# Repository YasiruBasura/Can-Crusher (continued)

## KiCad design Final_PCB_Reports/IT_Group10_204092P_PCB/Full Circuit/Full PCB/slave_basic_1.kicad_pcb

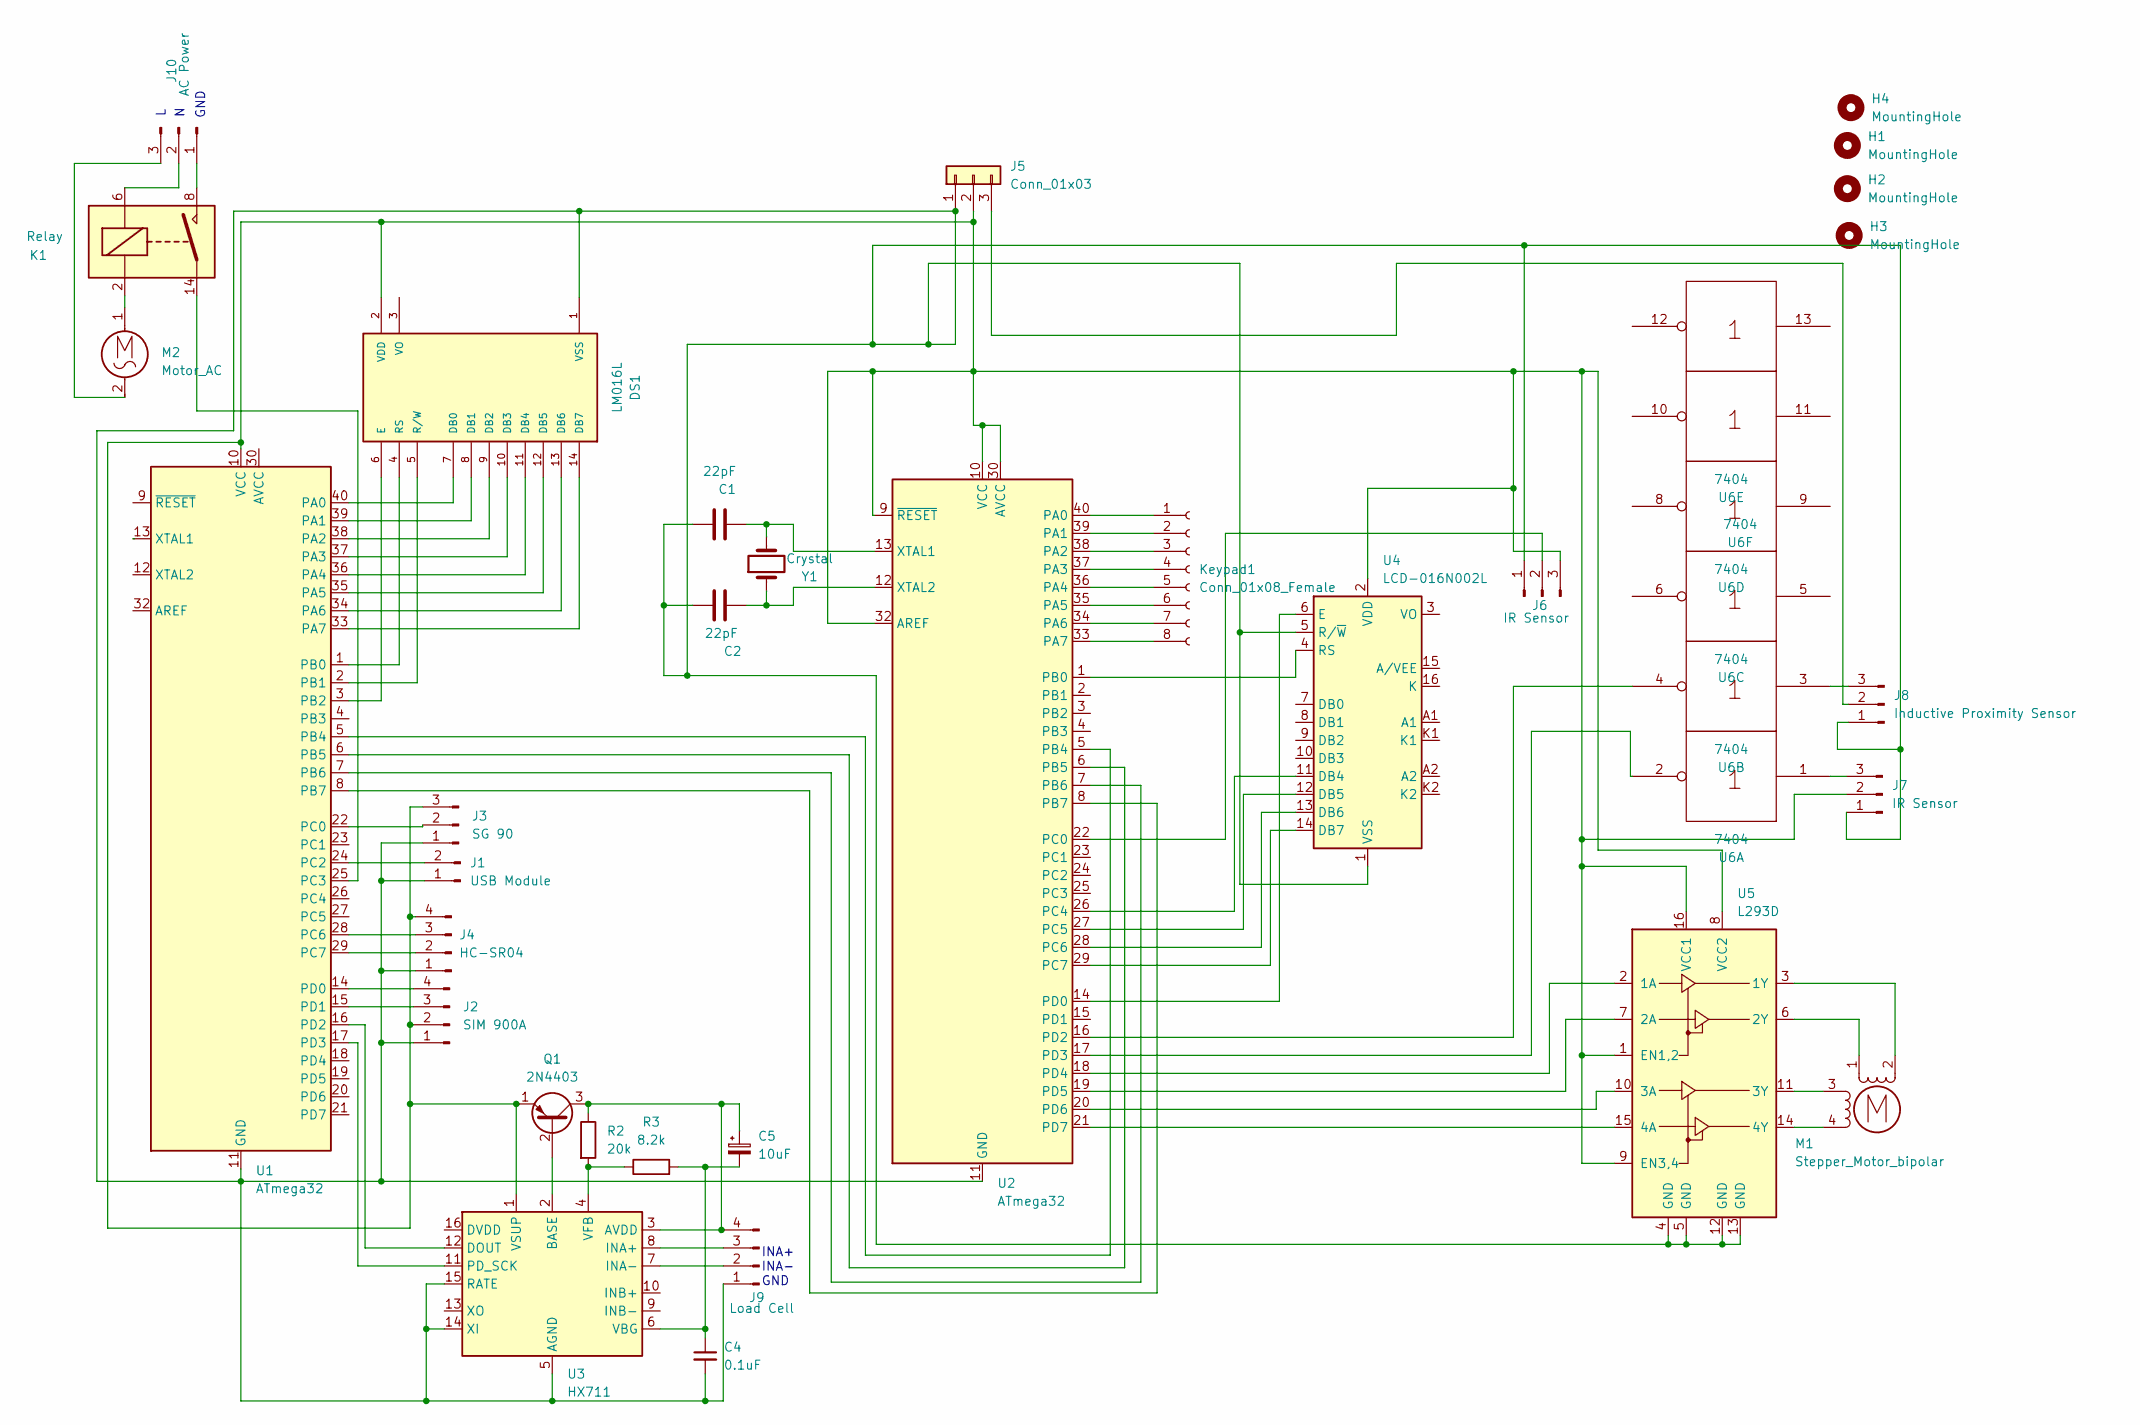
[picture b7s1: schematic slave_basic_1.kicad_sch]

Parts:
C1, C2: 22pF; CP_Radial_D4.0mm_P1.50mm
C4: 0.1uF; CP_Radial_D4.0mm_P1.50mm
C5: 10uF; CP_Radial_D4.0mm_P1.50mm
DS1: LM016L; LCD_LM016L
H1, H2, H3, H4: MountingHole; MountingHole_3.5mm_Pad
J1: USB Module; PinSocket_1x02_P1.27mm_Vertical
J2: SIM 900A; PinSocket_1x04_P1.27mm_Vertical
J3: SG 90; PinSocket_1x03_P1.27mm_Vertical
J4: HC-SR04; PinSocket_1x04_P1.27mm_Vertical
J5: Conn_01x03; PinSocket_1x03_P2.54mm_Vertical
J6, J7: IR Sensor; PinSocket_1x03_P1.27mm_Vertical
J8: Inductive Proximity Sensor; PinSocket_1x03_P1.27mm_Vertical
J9: Load Cell; PinSocket_1x04_P1.27mm_Vertical
J10: AC Power; PinSocket_1x03_P1.27mm_Vertical
K1: Relay; Relay_StandexMeder_DIP_LowProfile
Keypad1: Conn_01x08_Female; PinSocket_1x08_P1.27mm_Vertical
M1: Stepper_Motor_bipolar; PinSocket_1x04_P1.27mm_Vertical
M2: Motor_AC; PinSocket_1x02_P2.54mm_Vertical
Q1: 2N4403; TO-92_Inline
R2: 20k; R_Axial_DIN0204_L3.6mm_D1.6mm_P5.08mm_Horizontal
R3: 8.2k; R_Axial_DIN0204_L3.6mm_D1.6mm_P5.08mm_Horizontal
U1, U2: ATmega32; DIP-40_W15.24mm
U3: HX711; DIP-14_W7.62mm
U4: LCD-016N002L
U5: L293D; DIP-16_W7.62mm
U6: 7404; DIP-14_W7.62mm
Y1: Crystal; Crystal_AT310_D3.0mm_L10.0mm_Vertical

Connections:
Gnd: U6.7 (Gnd), U6.14 (Vcc)
unnamed: C1.1, C2.1, C4.2, DS1.1 (VSS), J1.1, J2.1, J3.1, J4.1, J5.1, J6.1, J7.1, J8.1, J9.1, U1.11 (GND), U1.31 (GND), U2.11 (GND), U2.31 (GND), U3.5 (AGND), U3.14 (XI), U3.15 (RATE), U4.1 (VSS), U4.5 (R/~W), U5.4 (GND), U5.5 (GND), U5.12 (GND), U5.13 (GND)
unnamed: C1.2, U2.13 (XTAL1), Y1.2
unnamed: C2.2, U2.12 (XTAL2), Y1.1
unnamed: C4.1, C5.2, R3.2, U3.6 (VBG)
unnamed: C5.1, J9.4, Q1.3 (C), R2.1, U3.3 (AVDD)
unnamed: DS1.2 (VDD), J2.2, J3.3, J4.4, J5.2, J6.3, J7.2, Q1.1 (E), U1.10 (VCC), U2.9 (~RESET), U2.10 (VCC), U2.30 (AVCC), U2.32 (AREF), U3.1 (VSUP), U4.2 (VDD), U5.1 (EN1,2), U5.8 (VCC2), U5.9 (EN3,4), U5.16 (VCC1)
unnamed: DS1.4 (RS), U1.1 (PB0)
unnamed: DS1.5 (R/W), U1.2 (PB1)
unnamed: DS1.6 (E), U1.3 (PB2)
unnamed: DS1.7 (DB0), U1.40 (PA0)
unnamed: DS1.8 (DB1), U1.39 (PA1)
unnamed: DS1.9 (DB2), U1.38 (PA2)
unnamed: DS1.10 (DB3), U1.37 (PA3)
unnamed: DS1.11 (DB4), U1.36 (PA4)
unnamed: DS1.12 (DB5), U1.35 (PA5)
unnamed: DS1.13 (DB6), U1.34 (PA6)
unnamed: DS1.14 (DB7), U1.33 (PA7)
unnamed: J1.2, U1.24 (PC2)
unnamed: J2.3, U1.15 (PD1)
unnamed: J2.4, U1.14 (PD0)
unnamed: J3.2, U1.22 (PC0)
unnamed: J4.2, U1.29 (PC7)
unnamed: J4.3, U1.28 (PC6)
unnamed: J5.3, J8.2
unnamed: J6.2, U2.22 (PC0)
unnamed: J7.3, U6.1
unnamed: J8.3, U6.3
unnamed: J10.1, K1.8
unnamed: J10.2, K1.6
unnamed: J10.3, M2.2
unnamed: K1.2, M2.1
unnamed: Keypad1.1, U2.40 (PA0)
unnamed: Keypad1.2, U2.39 (PA1)
unnamed: Keypad1.3, U2.38 (PA2)
unnamed: Keypad1.4, U2.37 (PA3)
unnamed: Keypad1.5, U2.36 (PA4)
unnamed: Keypad1.6, U2.35 (PA5)
unnamed: Keypad1.7, U2.34 (PA6)
unnamed: Keypad1.8, U2.33 (PA7)
unnamed: M1.1, U5.6 (2Y)
unnamed: M1.2 (-), U5.3 (1Y)
unnamed: M1.3, U5.11 (3Y)
unnamed: M1.4, U5.14 (4Y)
unnamed: Q1.2 (B), U3.2 (BASE)
unnamed: R2.2, R3.1, U3.4 (VFB)
unnamed: U1.5 (PB4), U2.5 (PB4)
unnamed: U1.6 (PB5), U2.6 (PB5)
unnamed: U1.7 (PB6), U2.7 (PB6)
unnamed: U1.8 (PB7), U2.8 (PB7)
unnamed: U1.16 (PD2), U3.12 (DOUT)
unnamed: U1.17 (PD3), U3.11 (PD_SCK)
unnamed: K1.14, U1.25 (PC3)
unnamed: U2.1 (PB0), U4.4 (RS)
unnamed: U2.14 (PD0), U4.6 (E)
unnamed: U2.16 (PD2), U6.4
unnamed: U2.17 (PD3), U6.2
unnamed: U2.18 (PD4), U5.2 (1A)
unnamed: U2.19 (PD5), U5.7 (2A)
unnamed: U2.20 (PD6), U5.10 (3A)
unnamed: U2.21 (PD7), U5.15 (4A)
unnamed: U2.26 (PC4), U4.11 (DB4)
unnamed: U2.27 (PC5), U4.12 (DB5)
unnamed: U2.28 (PC6), U4.13 (DB6)
unnamed: U2.29 (PC7), U4.14 (DB7)
unnamed: J9.2, U3.7 (INA-)
unnamed: J9.3, U3.8 (INA+)

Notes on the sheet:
INA+ INA- GND
GND

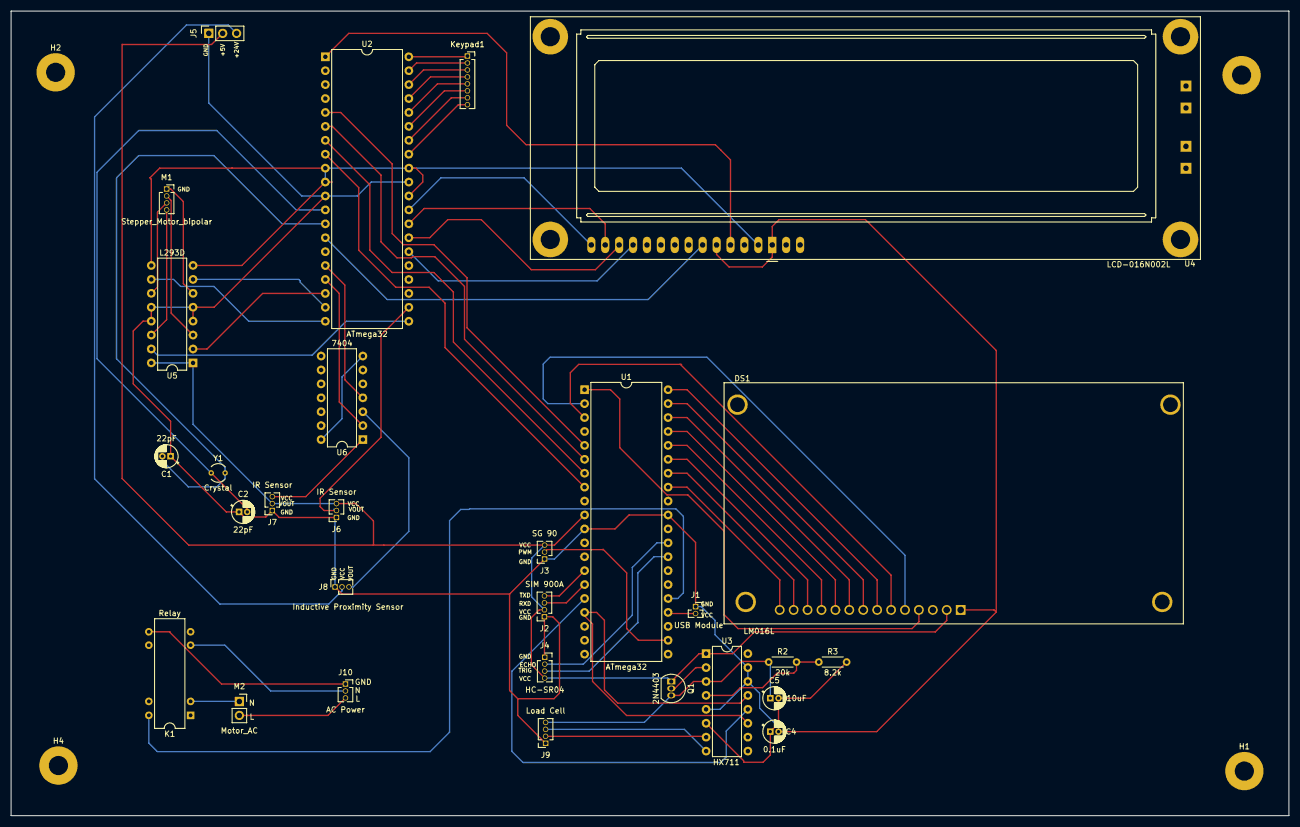
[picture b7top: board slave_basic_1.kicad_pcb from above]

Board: 2 copper layers, 233.2 x 146.8 mm, 33 parts (0 on the bottom side), 67 nets.

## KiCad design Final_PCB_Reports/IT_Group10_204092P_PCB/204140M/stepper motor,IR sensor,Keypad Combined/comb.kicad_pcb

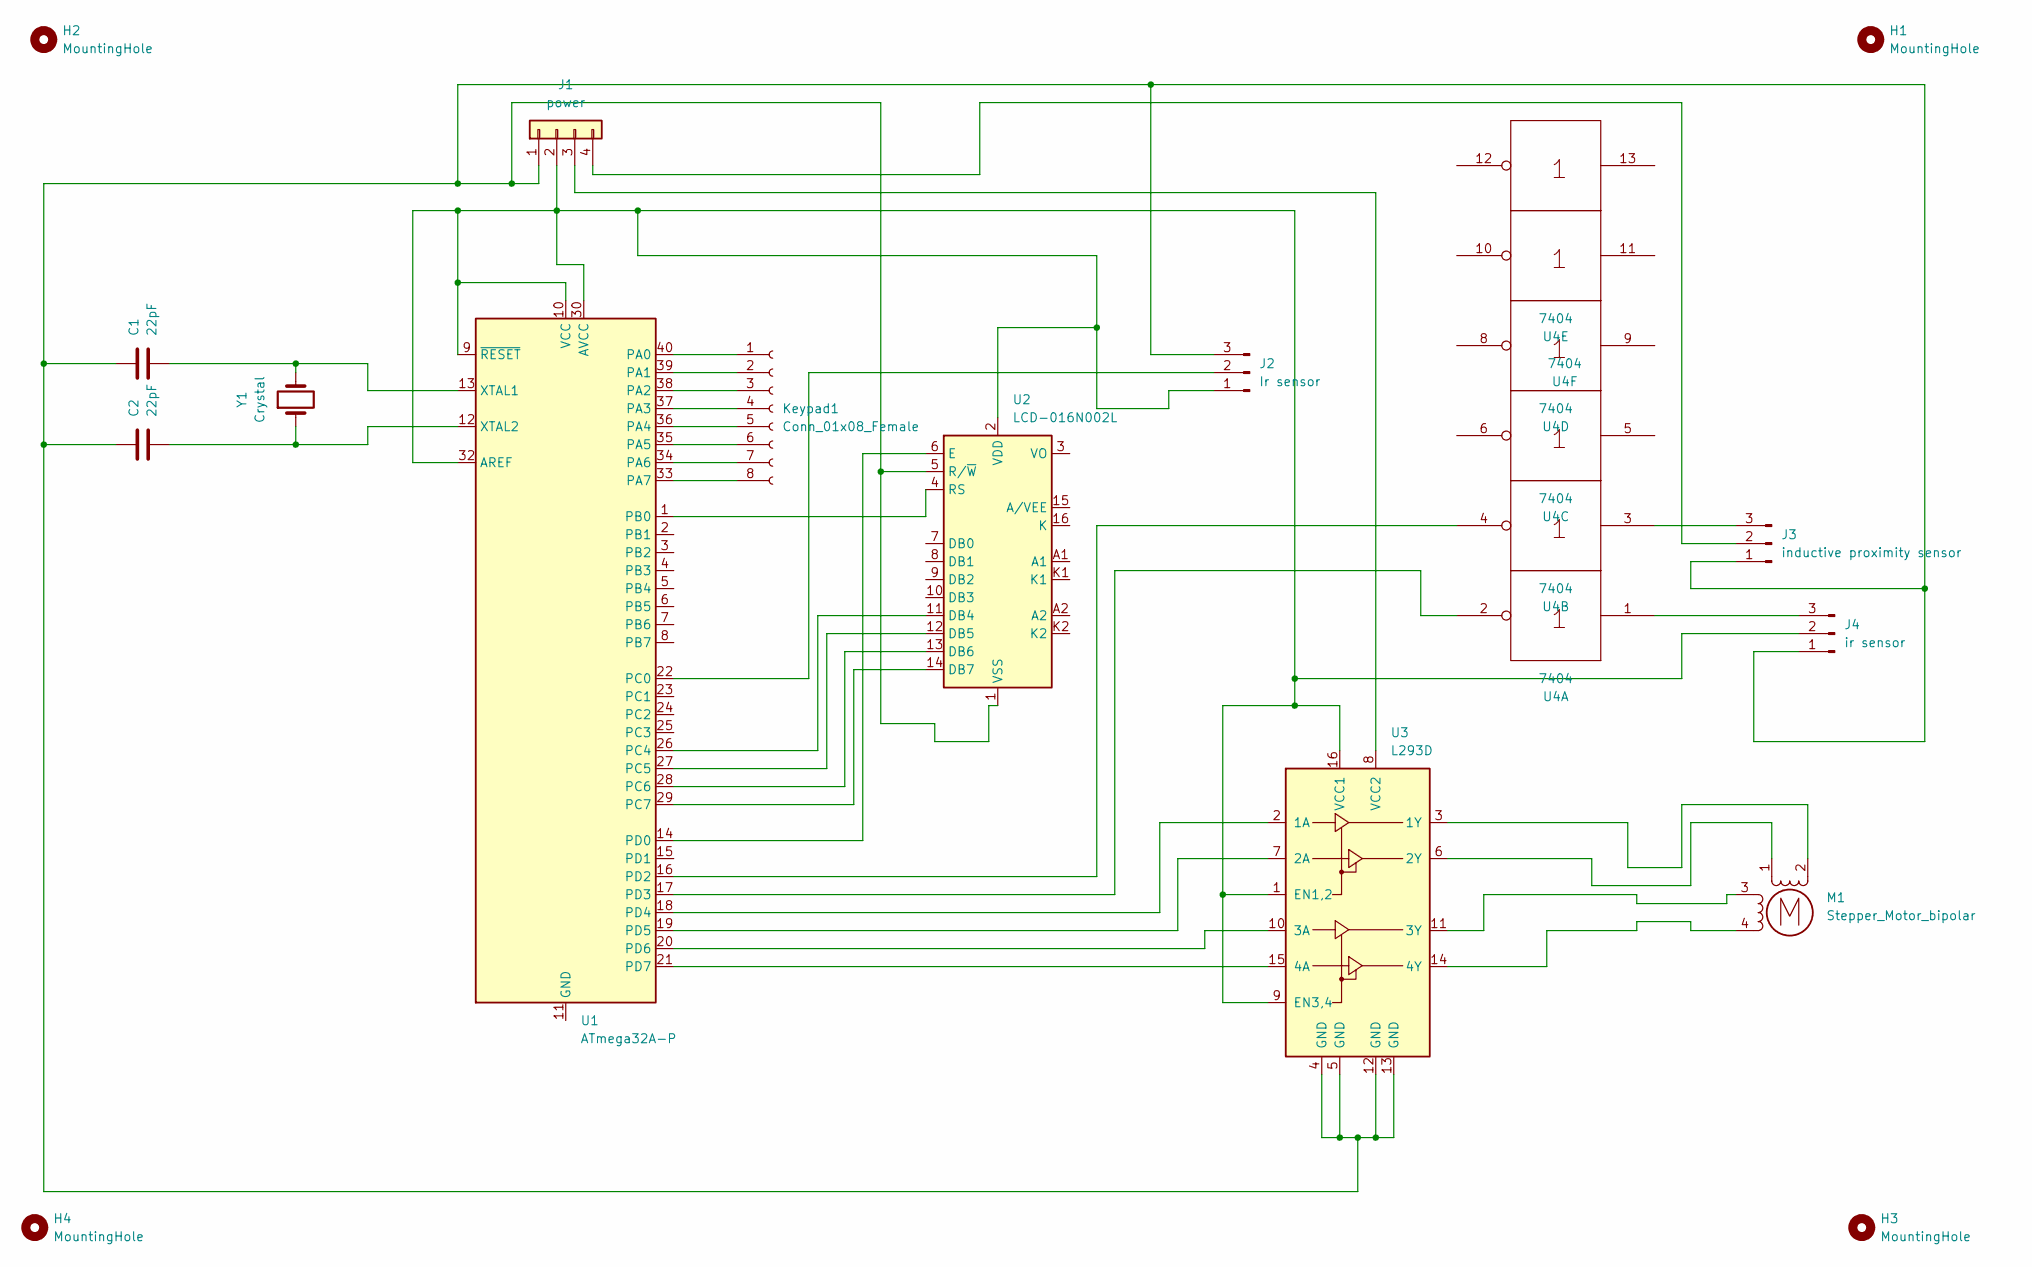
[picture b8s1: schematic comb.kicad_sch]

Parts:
C1, C2: 22pF; CP_Radial_D4.0mm_P1.50mm
H1, H2, H3, H4: MountingHole; MountingHole_3.5mm_Pad
J1: power; PinHeader_1x04_P2.54mm_Horizontal
J2: Ir sensor; PinSocket_1x03_P1.27mm_Vertical
J3: inductive proximity sensor; PinSocket_1x03_P1.27mm_Vertical
J4: ir sensor; PinSocket_1x03_P1.27mm_Vertical
Keypad1: Conn_01x08_Female; PinSocket_1x08_P1.27mm_Vertical
M1: Stepper_Motor_bipolar; PinSocket_1x04_P1.27mm_Vertical
U1: ATmega32A-P; DIP-40_W15.24mm
U2: LCD-016N002L
U3: L293D; DIP-16_W7.62mm
U4: 7404; DIP-14_W7.62mm
Y1: Crystal; Crystal_AT310_D3.0mm_L10.0mm_Vertical

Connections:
Gnd: U4.7 (Gnd), U4.14 (Vcc)
unnamed: C1.1, C2.1, J1.1, J2.3, J3.1, J4.1, U2.1 (VSS), U2.5 (R/~W), U3.4 (GND), U3.5 (GND), U3.12 (GND), U3.13 (GND)
unnamed: C1.2, U1.13 (XTAL1), Y1.2
unnamed: C2.2, U1.12 (XTAL2), Y1.1
unnamed: J1.2, J2.1, J4.2, U1.9 (~RESET), U1.10 (VCC), U1.30 (AVCC), U1.32 (AREF), U2.2 (VDD), U3.1 (EN1,2), U3.9 (EN3,4), U3.16 (VCC1)
unnamed: J1.3, U3.8 (VCC2)
unnamed: J1.4, J3.2
unnamed: J2.2, U1.22 (PC0)
unnamed: J3.3, U4.3
unnamed: J4.3, U4.1
unnamed: Keypad1.1, U1.40 (PA0)
unnamed: Keypad1.2, U1.39 (PA1)
unnamed: Keypad1.3, U1.38 (PA2)
unnamed: Keypad1.4, U1.37 (PA3)
unnamed: Keypad1.5, U1.36 (PA4)
unnamed: Keypad1.6, U1.35 (PA5)
unnamed: Keypad1.7, U1.34 (PA6)
unnamed: Keypad1.8, U1.33 (PA7)
unnamed: M1.1, U3.6 (2Y)
unnamed: M1.2 (-), U3.3 (1Y)
unnamed: M1.3, U3.11 (3Y)
unnamed: M1.4, U3.14 (4Y)
unnamed: U1.1 (PB0), U2.4 (RS)
unnamed: U1.11 (GND), U1.31 (GND)
unnamed: U1.14 (PD0), U2.6 (E)
unnamed: U1.16 (PD2), U4.4
unnamed: U1.17 (PD3), U4.2
unnamed: U1.18 (PD4), U3.2 (1A)
unnamed: U1.19 (PD5), U3.7 (2A)
unnamed: U1.20 (PD6), U3.10 (3A)
unnamed: U1.21 (PD7), U3.15 (4A)
unnamed: U1.26 (PC4), U2.11 (DB4)
unnamed: U1.27 (PC5), U2.12 (DB5)
unnamed: U1.28 (PC6), U2.13 (DB6)
unnamed: U1.29 (PC7), U2.14 (DB7)

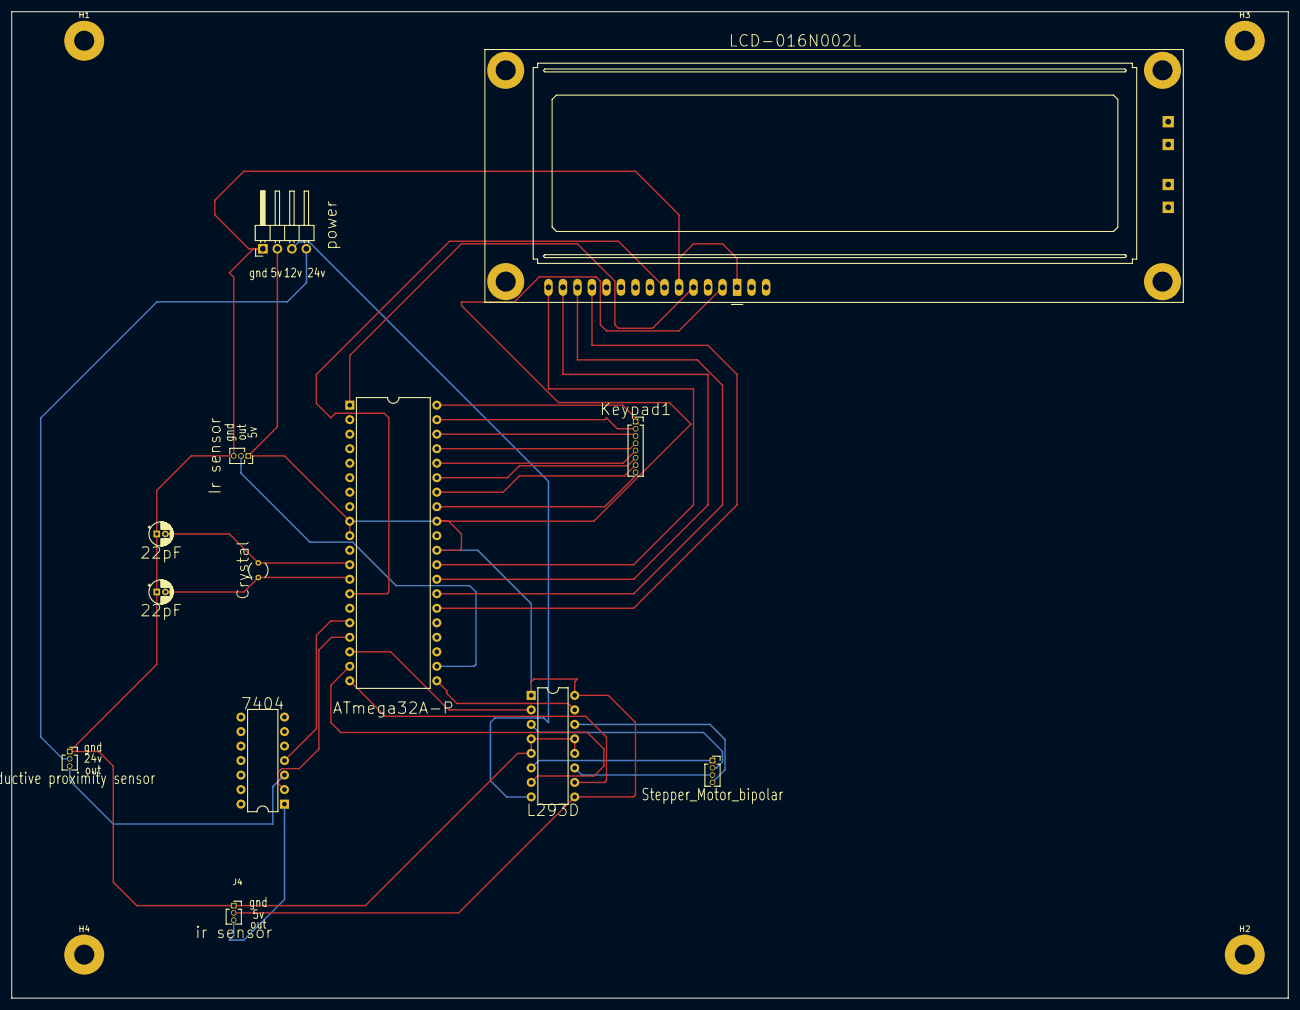
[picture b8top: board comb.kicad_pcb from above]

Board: 2 copper layers, 223.5 x 172.7 mm, 17 parts (0 on the bottom side), 35 nets.

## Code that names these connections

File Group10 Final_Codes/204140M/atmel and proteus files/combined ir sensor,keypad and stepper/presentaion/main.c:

#ifndef F_CPU

#define F_CPU 16000000UL //freaquency of external crystal

#endif
#include <avr/io.h>
#include <util/delay.h>



//define interfacing pins between L293D and ATmega32

#define a1 (1<<PD4)

#define a2 (1<<PD5)

#define a3 (1<<PD6)

#define a4  (1<<PD7)



//For switch

#define SW (1<<PD3)    //Ir
#define SW2 (1<<PD2)   //ALL validation

//lcd and key board
#define LCD PORTC
#define EN 0
#define RS 0
#define RW 1

 int get_pn;
 //int get_cn;//number of cans
 char can_no[10];
 

unsigned char keypad();
int keypad_func(){
	unsigned char x;
	char no[10];
	int i=0;
	int i1=0;
	DDRA =0x0F; // make PA0 to PA3 = output and PA4 to PA7 = Input
	lcd_init();
	while(1){
		PORTA=0xF0; // make all 4 column 1 and all rows 0
		if(PINA!= 0xF0){
			_delay_ms(5);
			x=keypad();
			if (x=='*')
			{
				lcdcmd(0x01);//clear lcd
				lcdcmd(0x80);//set the curser to first line
				lcd_Print("1-Fast Charge");
				lcdcmd(0xc0);//set the curser to second line
				lcd_Print("2-Ez Cash");
				_delay_ms(100);
				lcdcmd(0x01);
				lcdcmd(0x80);//set the curser to first line
				lcd_Print("3-Donate");
				
				while(1){
					if(PINA!= 0xF0){
						x=keypad();
						//charge
						if(x=='1'){
							_delay_ms(5);
							lcdcmd(0x80);//set the curser to first line
							lcd_Print(" ");
							lcdcmd(0x01);//clear lcd
							break;
						}
						//easy cash
						else if(x=='2'){
							get_pn=1;//get phone no
							_delay_ms(5);
							lcdcmd(0x80);//set the curser to first line
							lcd_Print(" ");
							lcdcmd(0x01);//clear lcd
							lcd_Print("Enter the Phone");
							lcdcmd(0xc0);
							lcd_Print("Number");
							lcdcmd(0x80);
							_delay_ms(100);
							lcdcmd(0x01);
							lcd_Print("Press = to");
							lcdcmd(0xc0);
							lcd_Print("Finish");
							lcdcmd(0x80);
							_delay_ms(100);
							lcdcmd(0x01);
							break;
						}
						//donate
						else if(x=='3'){
							
						}
						
					}
					/*else
					{
						lcddata(x);
						
					}*/

				}
				
				
			}
			else if (x=='=')
			{
				
				
				get_pn=0;
				lcdcmd(0x01);
				lcd_Print("Entered phone NO.:");
				lcdcmd(0xc0);
				lcd_Print(&no);//print the no
				lcdcmd(0x80);
				//lcd_Print(&can_no);//print the no
				int phone_no= atoi(no);//phone nimber in int
				_delay_ms(100);
				lcdcmd(0x01);
			
				_delay_ms(100);
				lcdcmd(0x01);
				i=0;
				return 0;
				
				
			}
			else
			{
				
				lcddata(x);
				if(get_pn==1){
					no[i]=x;
					i++;
				}
				else{
					can_no[i1]=x;
					i1++;
				}
				
			}
		}
	}
	
}
void lcdcmd(unsigned char cmd){
	PORTB &=~(1<<RS); //RS=0 for command (1111 1110)
	PORTB &=~(1<<RW); //RW=0 for write (1111 1101)
	LCD= cmd & 0xF0;  //Send upper nibble
	PORTD|=(1<<EN); //EN=1 for H to L pulse
	_delay_ms(1);
	PORTD &= ~(1<<EN); // EN=0 for H to L pulse

	LCD = cmd<<4; // send low nibble;
	PORTD |=(1<<EN); //EN=0for H to L pulse
	_delay_ms(1);
	PORTD &= ~(1<<EN);
}

void lcd_Print (char*str){
	int i;
	for(i=0;str[i]!=0;i++)		/* Send each char of string till the NULL */
	{
		lcddata(str[i]);
	}
}


void lcddata(unsigned char data){
	PORTB |= (1<<RS); //RS=1 for data
	PORTB &= ~(1<<RW); //RW=0 for write
	LCD= data & 0xF0;  //Send upper nibble
	PORTD|= (1<<EN); //EN=1 for H to L pulse
	_delay_ms(5);
	PORTD &= ~(1<<EN); // EN=0 for H to L pulse

	LCD = data<<4; // send low nibble;
	PORTD |=(1<<EN); //EN=1 for H to L pulse
	_delay_ms(5);
	PORTD &= ~(1<<EN);
	
}

void lcd_init(){
	//DDRC= 0xFF;
	DDRC= 0xF0; // Define  output LCD port(ALL c ports are outputs) 
	DDRD |=(1<<EN); //Define EN pin  as output
	DDRB=0xFF; // define RS and  RW pin as output
	PORTD&= ~(1<<EN); //initialize EN=0
	lcdcmd(0x33);
	lcdcmd(0x32);
	lcdcmd(0x28); // LCD in 4 bit mode
	lcdcmd(0x0E); //display on cursor on
	/*lcddata(72);
	lcddata(69);
	lcddata(76);
	lcddata(76);
	lcddata(79);*/
	lcd_Print("WELCOME");
	_delay_ms(40);
	lcdcmd(0x01); //clear LCD
	lcd_Print("Enter the Number");
    lcdcmd(0xc0);//set the curser to second line 
	lcd_Print("of cans and");
	_delay_ms(40);
	lcdcmd(0x01); //clear LCD
	lcdcmd(0x80);//set the curser to first line 
	lcd_Print("Press + to start");
	_delay_ms(40);
	 lcdcmd(0xc0);//set the curser to second line
	 lcd_Print("the process : ");
	  //lcdcmd(0x80);
	 
}

unsigned char keypad(){
	PORTA=0b11111110; // make 1st row 0
	if((PINA & (1<<PINA4))==0){
		_delay_ms(3);
		return '7';
		}else if((PINA & (1<<PINA5))==0){
		_delay_ms(3);
		return '8';
		}else if((PINA & (1<<PINA6))==0){
		_delay_ms(3);
		return '9';
		}else if((PINA & (1<<PINA7))==0){
		_delay_ms(3);
		return '/';
	}
	PORTA=0b11111101;
	if((PINA & (1<<PINA4))==0){
		_delay_ms(3);
		return '4';
		}else if((PINA & (1<<PINA5))==0){
		_delay_ms(3);
		return '5';
		}else if((PINA & (1<<PINA6))==0){
		_delay_ms(3);
		return '6';
		}else if((PINA & (1<<PINA7))==0){
		_delay_ms(3);
		return '+';
	}
	PORTA=0b11111011;
	if((PINA & (1<<PINA4))==0){
		_delay_ms(3);
		return '1';
		}else if((PINA & (1<<PINA5))==0){
		_delay_ms(3);
		return '2';
		}else if((PINA & (1<<PINA6))==0){
		_delay_ms(3);
		return '3';
		}else if((PINA & (1<<PINA7))==0){
		_delay_ms(3);
		return '-';
	}
	PORTA=0b11110111;
	if((PINA & (1<<PINA4))==0){
		_delay_ms(3);
		return 'C';
		}else if((PINA & (1<<PINA5))==0){
		_delay_ms(3);
		return '0';
		}else if((PINA & (1<<PINA6))==0){
		_delay_ms(3);
		return '=';
		}else if((PINA & (1<<PINA7))==0){
		_delay_ms(3);
		return '*';
	}
}

int Stepper_motor(){
	
   


	
	//Set a1, a2, a3, a4 as output

	DDRD |= a1 | a2 | a3| a4;

	//Set input & pull-up resistor

	DDRD &= ~SW;

	PORTD |= SW;
	
	DDRD &= ~SW2;

	PORTD |= SW2;
	
	while(1){
		
		if((PIND & SW) && (PIND & SW2)){

			while(1){
				
				if((!(PIND & SW2))){
					while(1){
						if((!(PIND & SW))){
							PORTD |= a1;

							PORTD &= ~a2;

							PORTD &= ~a3;

							PORTD &= ~a4;

							_delay_ms(20);



							PORTD |= a1;

							PORTD &= ~a2;

							PORTD  &= ~ a3;

							PORTD |= a4;

							_delay_ms(4);
							
							

							
							PORTD &= ~a1;

							PORTD &= ~a2;

							PORTD &= ~a3;

							PORTD |= a4;

							_delay_ms(20);
							
							
							PORTD |= a1;

							PORTD &= ~a2;

							PORTD &= ~ a3;

							PORTD |= a4;

							_delay_ms(4);
							
							
							
							PORTD |= a1;

							PORTD &= ~a2;

							PORTD &= ~a3;

							PORTD &= ~a4;

							_delay_ms(20);
							return 0;
						}
					}

					


					

				}
				

				else if(!(PIND & SW)){

					

					


					PORTD |= a1;

					PORTD &= ~a2;

					PORTD &= ~a3;

					PORTD &= ~a4;

					_delay_ms(20);



					PORTD |= a1;

					PORTD &= ~a2;

					PORTD |= a3;

					PORTD &= ~a4;

					_delay_ms(4);
					
					

					
					PORTD &= ~a1;

					PORTD &= ~a2;

					PORTD |= a3;

					PORTD &= ~a4;

					_delay_ms(20);
					
					
					PORTD |= a1;

					PORTD &= ~a2;

					PORTD |= a3;

					PORTD &= ~a4;

					_delay_ms(4);
					
					
					
					PORTD |= a1;

					PORTD &= ~a2;

					PORTD &= ~a3;

					PORTD &= ~a4;

					_delay_ms(20);
					

					

					return 0;
				}

				

			}
			
		}
	}

	
	
	
}
int main(void){
    while(1){
		keypad_func();
		int can_number= atoi(can_no);
		for(int k=0;k<can_number;k++){
			Stepper_motor();
		}
			
	}
	
	return 0;
}

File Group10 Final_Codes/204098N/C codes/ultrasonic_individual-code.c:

#define F_CPU 16000000UL
#include <avr/io.h>            // Include AVR std. library file 
#include <util/delay.h>        
#include <stdlib.h>            //convert integer to character array 

#define lcd_port PORTD          // connected lcd on to the port D
#define lcd_data_dir  DDRD      // difinding the direction of the pins- input/out
#define rs PD0                  
#define en PD1     
             
#define US_PORT PORTC           // connected ultrasonic to port C
#define	US_PIN	PINC            // initialization of pin register
#define US_DDR 	DDRC            // data direction register to set the data direction flow 

#define US_TRIG_POS	PC0          
#define US_ECHO_POS	PC1        


#define US_ERROR		-1     //difinding variable to  working or not
#define	US_NO_OBSTACLE	-2

int distance, previous_distance;




void HCSR04Init();
void HCSR04Trigger();

void lcd_command( unsigned char );

void HCSR04Init()
{
	
	
	US_DDR|=(1<<US_TRIG_POS);
}

void HCSR04Trigger()
{  
	
	US_PORT|=(1<<US_TRIG_POS);	
	
	_delay_us(15);				
	
	US_PORT&=~(1<<US_TRIG_POS);	
}

uint16_t GetPulseWidth()
{
	
	
	uint32_t i,result;


	for(i=0;i<600000;i++)
	{
		if(!(US_PIN & (1<<US_ECHO_POS)))
		continue;	
		else
		break;		
	}

	if(i==600000)
	return US_ERROR;	
	
	TCCR1A=0X00;
	TCCR1B=(1<<CS11);	
	TCNT1=0x00;			

	
	for(i=0;i<600000;i++)              
	{
		if(US_PIN & (1<<US_ECHO_POS))
		{
			if(TCNT1 > 60000) break; else continue;  
		}
		else
		break;
	}

	if(i==600000)
	return US_NO_OBSTACLE;	

	

	result=TCNT1;          

	
	TCCR1B=0x00;

	if(result > 60000)
	return US_NO_OBSTACLE;	
	else
	return (result>>1);
}



void initialize (void)
{
	lcd_data_dir = 0xFF;     //lcd pins that connected to micro-controller as out puts
	_delay_ms(15);           
	lcd_command(0x02);       
	lcd_command(0x28);      
	lcd_command(0x0c);
	lcd_command(0x06);
	lcd_command(0x01);
	_delay_ms(2);
}

void lcd_command( unsigned char cmnd )
{

	lcd_port = (lcd_port & 0x0F) | (cmnd & 0xF0);  
	lcd_port &= ~ (1<<rs);
	lcd_port |= (1<<en);
	_delay_us(1);
	lcd_port &= ~ (1<<en);
	
	
	_delay_us(200);
	
	
	lcd_port = (lcd_port & 0x0F) | (cmnd << 4);
	lcd_port |= (1<<en);
	_delay_us(1);
	lcd_port &= ~ (1<<en);
	_delay_ms(2);
}

void lcd_clear()
{
	lcd_command (0x01);   
	_delay_ms(2);        
	lcd_command (0x80);   
}


void lcd_print (char *str)
{
	
	int i;
	for(i=0; str[i]!=0; i++)
	{
		
		lcd_port = (lcd_port & 0x0F) | (str[i] & 0xF0);
		lcd_port |= (1<<rs);
		lcd_port|= (1<<en);
		_delay_us(1);
		lcd_port &= ~ (1<<en);
		_delay_us(200);
		lcd_port = (lcd_port & 0x0F) | (str[i] << 4);
		lcd_port |= (1<<en);
		_delay_us(1);
		lcd_port &= ~ (1<<en);
		_delay_ms(2);
	}
}



void lcd_setCursor(unsigned char x, unsigned char y){    
	unsigned char adr[] = {0x80, 0xC0};    
	lcd_command(adr[y-1] + x-1);
	_delay_us(100);
}

int main()
{
	initialize();           

	char numberString[4];   

	while(1) {
		
		uint16_t r;
		
		_delay_ms(100);


		
		
		HCSR04Init();  // set io port direction of sensor


		  
		lcd_print("hello customer !");
		_delay_ms(10);
		lcd_setCursor(1, 2); 
		lcd_print("enter your can");
		_delay_ms(1000);
		lcd_clear();                                             
		while(1)
		{
			
			HCSR04Trigger();     // calling the ultrasonic sound wave generator function
			
			r=GetPulseWidth();      // getting the duration of the ultrasound took echo back
       
	        // handle errors
			if(r==US_ERROR)               
			{
				lcd_setCursor(1, 1);     
				lcd_print("Error!");
			}
			else
			{
				
				distance=(r*0.034/2.0);	
				
				
				if (distance != previous_distance)    
				{
					lcd_clear();
				}
				
				lcd_setCursor(1, 1);  
				   
				
				if((distance>45)&&(distance<50))
				{
					lcd_setCursor(1, 1); 
					lcd_print("can  detected");
					
				}
				else
				{
					lcd_setCursor(3, 1); 
					lcd_print("can not detected");
				}
				
				     
				itoa(distance, numberString, 10);   // converting
				lcd_setCursor(8, 2);  
				lcd_print(numberString); 
				lcd_setCursor(10, 2);   
				lcd_print(" cm");
				
				
				
				
				previous_distance = distance;
				_delay_ms(30);
			}
		}
		
	}
}

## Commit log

2023-11-01 Final Commit
